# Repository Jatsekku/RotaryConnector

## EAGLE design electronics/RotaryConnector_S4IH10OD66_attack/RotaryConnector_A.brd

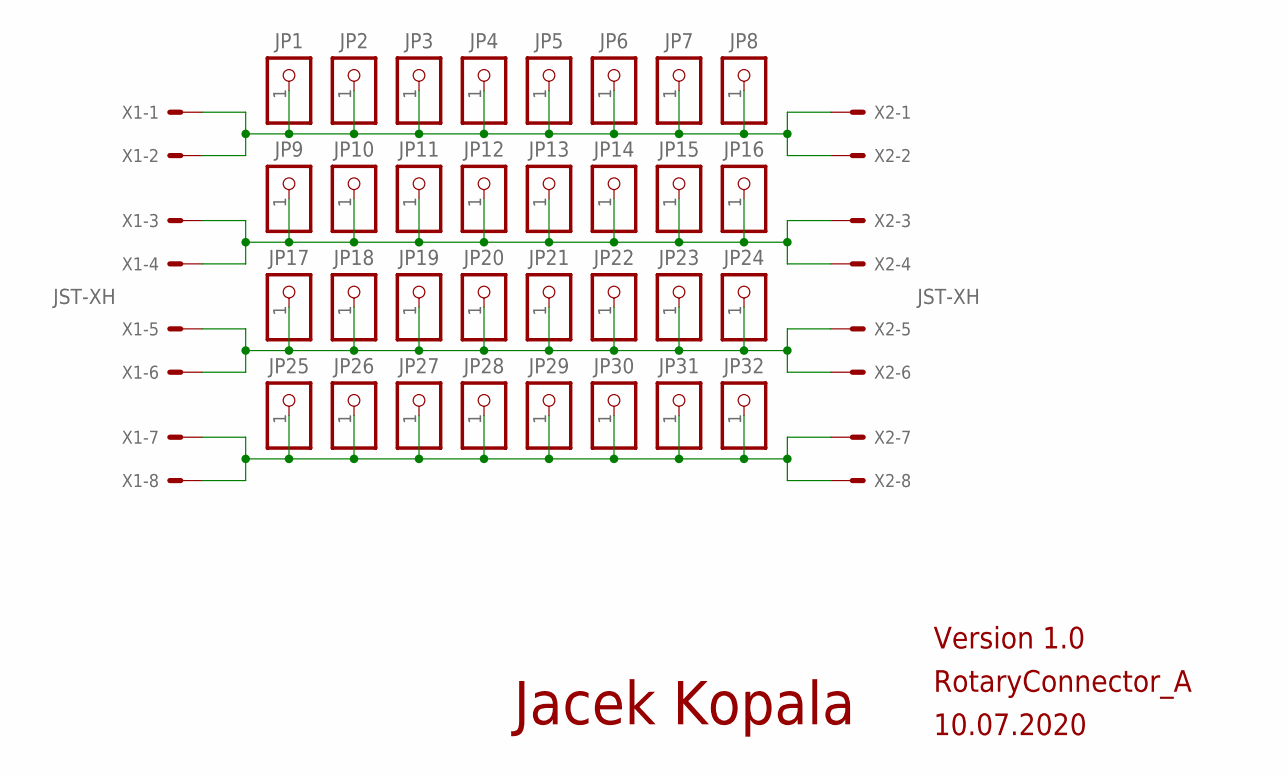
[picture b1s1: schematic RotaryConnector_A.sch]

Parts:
JP1, JP2, JP3, JP4, JP5, JP6, JP7, JP8, JP9, JP10, JP11, JP12, JP13, JP14, JP15, JP16, JP17, JP18, JP19, JP20, JP21, JP22, JP23, JP24, JP25, JP26, JP27, JP28, JP29, JP30, JP31, JP32: PINHD-1X1; 1X01
X1, X2: JST-XH; JST-XH-08-PACKAGE-LONG-PAD

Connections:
SIG1: JP1.1, JP2.1, JP3.1, JP4.1, JP5.1, JP6.1, JP7.1, JP8.1, X1.1, X1.2, X2.1, X2.2
SIG2: JP9.1, JP10.1, JP11.1, JP12.1, JP13.1, JP14.1, JP15.1, JP16.1, X1.3, X1.4, X2.3, X2.4
SIG3: JP17.1, JP18.1, JP19.1, JP20.1, JP21.1, JP22.1, JP23.1, JP24.1, X1.5, X1.6, X2.5, X2.6
SIG4: JP25.1, JP26.1, JP27.1, JP28.1, JP29.1, JP30.1, JP31.1, JP32.1, X1.7, X1.8, X2.7, X2.8

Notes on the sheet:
RotaryConnector_A
10.07.2020
Version 1.0
Jacek Kopala

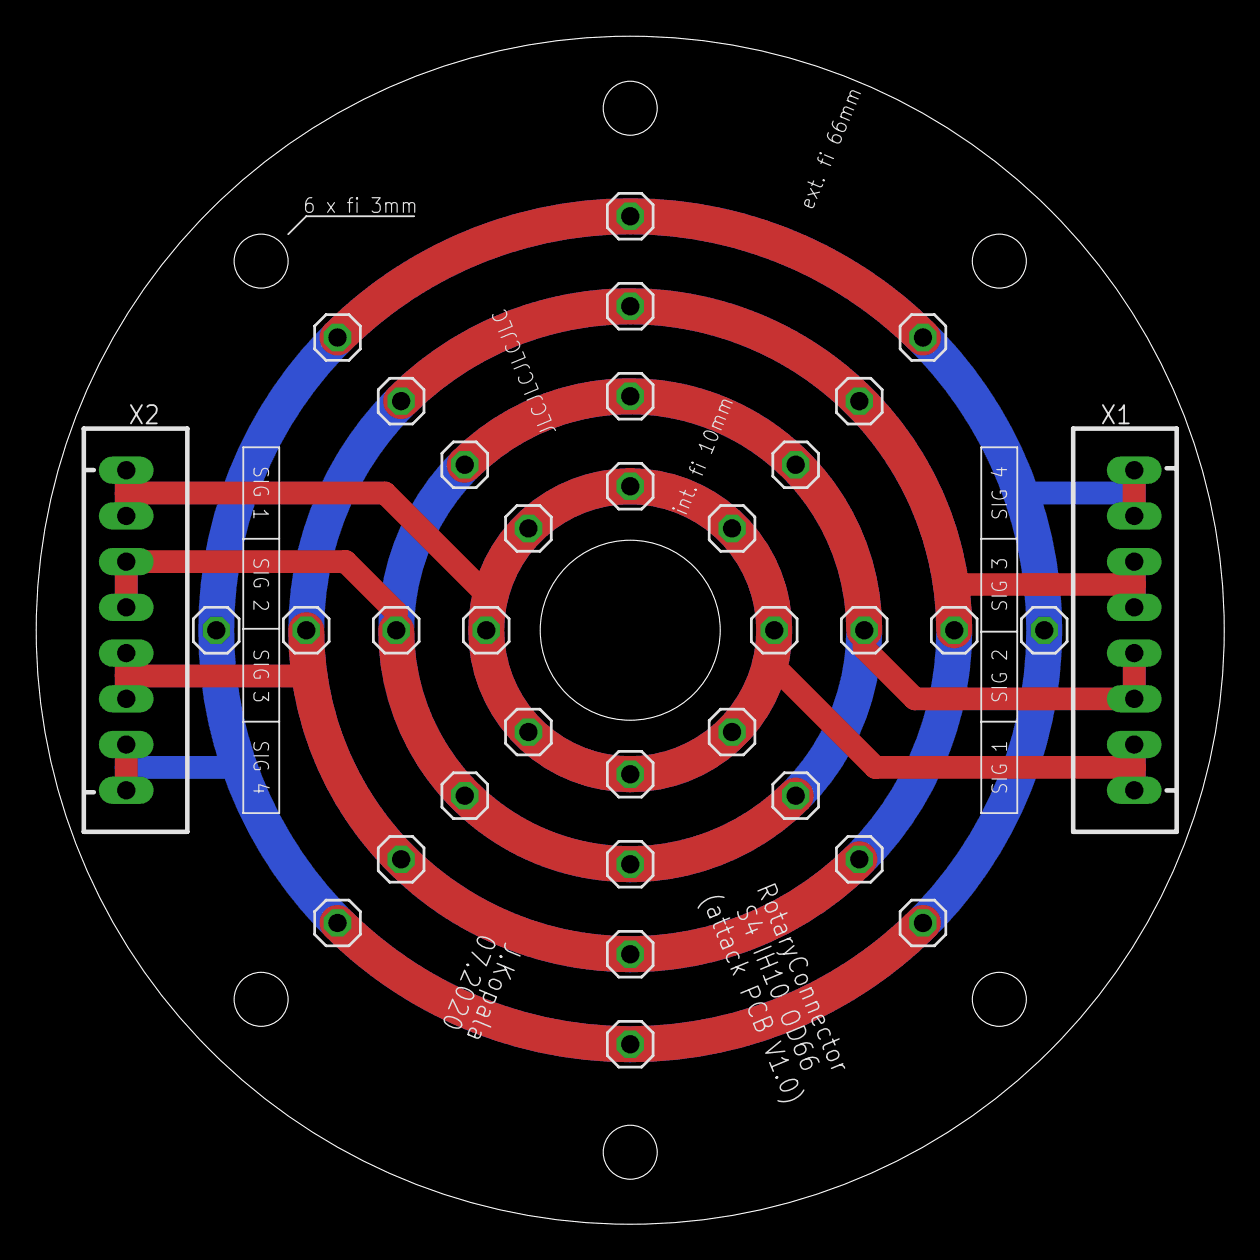
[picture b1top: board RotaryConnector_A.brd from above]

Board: 2 copper layers, 66.0 x 66.0 mm, 34 parts (0 on the bottom side), 4 nets.

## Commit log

2022-08-29 [electronics] Add schematics and PCB designs
    - XXX_attack directory is provided for the connector part where pogo pins will be placed,
    - XXX_receiving direcotory is provided for the connector part with sliding traces.
    Symbol S4IH10OD66 means:
    - S4 => signals: 4
    - IH10 => Inner hole: 10mm
    - OD66 => outer diameter: 66mm
